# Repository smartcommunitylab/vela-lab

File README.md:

##Smart City Vela Lab
========================

This repository contains the code for the network devices used in the Smart City Lab located in Vela (Trento, Italy).

For cloning:
```bash
git clone https://github.com/smartcommunitylab/vela-lab.git
cd vela-lab
git checkout ota
git submodule init
git submodule update
cd network_board/contiki-ng
git submodule init
git submodule update
```
Some detail about compilation can be found in README-BUILDING.md

The network components are:
- BLE Beacons: Eddystone or CLIMB (https://www.smartcommunitylab.it/climb-en/) proprietary beacons
- Vela Node: composed by:
    - BLE Scanner: Nordic nRF52 DK (nRF52832 SoC) - also referred as Nordic Board
    - Mesh Node: Texas Instruments cc2650/cc1350 launchpad - also referred as TI Board
    - Interface Board (provides mechanical and electrical connection between the BLE Scanner and the Mesh Node, moreover it manages the solar charger and the battery)
- Mesh Sink: Texas Instruments cc2650/cc1350 launchpad or sensortag
- Gateway: Raspberry PI

The purpose of the network is to monitor for the presence of BLE Beacons nearby the Vela Nodes. The list of presence (ble report) is sent to the sink by the means of the multihop network.
For each BLE Beacon detected by a Vela Node an entry is added to the ble report, this entry contains: the eddystone instance ID, the last value of the RSSI, the max value of the RSSI (during the last observation window) and the amount of beacons packets received from that beacon.
The ble report is generated by the BLE Scanner in particular the related code is in (vela-lab/bt_board/ble_app_vela_lab/main.c -> add_node_to_report_payload(...)).

The BLE Scanner and Mesh Node communicate through an interface based on UART periphearl. A specific communication protocol have been developed, the protocol implementation is in vela-lab/common/lib/uart_util.
The same implementation of this protocol (uart_util) is used both in the BLE Scanner and in the Mesh Node, the adaption of the interface with the proprietary stacks (contiki and nRF SDK) is made through macros (#ifdef CONTIKI #else #endif).

The packet format used by uart_util is briefly documented in vela-lab/doc/raw/uart_packet_struct.xlsx. The most important thing here is that the packet (excluding START_CHAR and END_OF_PACKET) is coded as hexadecimal string.
This means that every raw byte to transfer between the nordic and the TI is converted into two ascii characters (two bytes). It is equivalent to the use of sprintf(coded_byte,"%02x",raw_byte). In this way, the packets over the uart will contain only characters '0' (ascii 0x30) to '9' (ascii 0x39) and 'A' (ascii 0x41)  to 'F' (ascii 0x46).
The packet coding with hex string permits to safetly use START_CHAR=STX (ascii 0x02) and END_OF_PACKET='\n' (ascii 0x0A). Before the adoption of this coding, the packet containing a raw value 10 = 0x0A at any position was a problem since 0x0A is '\n' and it was processed as an END_OF_PACKET.
With hex coding a raw 0x0A (1 byte) is converted into two chars, '0' and 'A' which, in ascii are represented by two bytes: {0x30, 0x39}.

By employing the packet structure in uart_packet_struct.xlsx, debug printf output can be safetly merged with uart_util communication on the same UART interface without any (apparent) issues.
Another benefit of this protocol is that the communication can be sniffed and monitored with a standard serial terminal. Typically, when raw bytes are transmitted over a uart, the serial terminals (putty/teraterm) show only garbage, while using hex string any serial monitor can show the frames perfectly.

The types of packet and their payload description are documented in vela-lab/doc/raw/uart_cmd_def_velaLab.xlsx, these are the only commands that are supported in the communication between the TI and the Nordic over the UART interface. 
Even if there are similarities, the UART commands are not the same as the network commands. Network commands are issued by the Mesh Sink to the Mesh Nodes and they are documented in vela-lab/doc/raw/network_commands.xlsx while the actual definition of codes is in /common/inc/network_messages.h

The Mesh Sink is the root of the WSN and it is its the point where data comes out (for instance the bluetooth reports) or goes in (for instance network commands such as setting the keepalive interval).
Regardless the direction (WSN to gateway, or gateway to WSN) for most of the packet types, the sink just passes them, for some (for instance the ota related packets) some procedures, such as the spitting into smaller chunks, are executed.

Finally, the whole system is managed by the Gateway (which can be a standard pc as well as a single board computer such as a Raspberry) connected to the Mesh Sink running a python script (developed for python3).
On the raspberry, the embedded uart (/dev/ttyS0), exposed on the expansion header, can be used directly on the sensortag (given a proper connection of the TX/RX/Power pins).
Alternatively a launchpad can be used since it embeds a uart to usb bridge (typically /dev/ttyACM0), in that case no hardware related operation is required.

Again, the communication protocol over the UART between the Sink and the Gateway exploits hexadecimal string coding. 
The packet structure is as follow (it is not elsewhere documented): `<IPV6_ADDR_16_BYTES*><PAYLOAD_SIZE_1_BYTE><PACKET_TYPE_2_BYTES**><PAYLOAD_N_BYTES***><PAYLOAD_CHECKSUM_1_BYTE><'\n'>`

\* for broadcast packets (most of commands) set it to 0xFFFFFFFFFFFFFFFFFFFF, otherwise the ipv6 address of the destination node (the Sink cannot be addressed)'

\** these are the same as in vela-lab/doc/raw/network_commands.xlsx

\*** the maximum size of this is given by the uart buffer size defined by the SERIAL_LINE_CONF_BUFSIZE, for the Sink this is defined in in vela-lab/network_board/integrate_sender_uart/build_sink.sh.

Since the data is coded with hex string (2 bytes are allocated for each raw byte), the maximum size for the uart packet (including all the fields) is:  SERIAL_LINE_CONF_BUFSIZE/2.

The python script (vela-lab/gateway/dev/sink_integration/main.py) reads the incoming uart data and decode the packets. A basic Command Line interface is implemented, where basic informations about the WSN is displayed on top, while a console shows log messages.
The python script is lauched by navigating to vela-lab/gateway/dev/sink_integration/ and executing "python3 main.py /dev/ttyS0 57600", where /dev/ttyS0 can be changed with the proper port, and 57600 can be changed if the baudrate of the uart is changed on the Sink. However a simpler way is just to launch startup.sh in the repository root. The idea is to permanently store the default launch parameters (serial interface name, baudrate) into that script.
Once the script is launched, as soon as the data start to arrive from the WSN, the terminal interface becomes populated, by pressing h+enter the list of allowed commands is displayed.
Some command have parameters to be set (for instance the BLE scan parameters can be set), however for now the Command Line Interface does not allow to input the parameters that are hardcoded into vela-lab/gateway/dev/sink_integration/main.py (inside USER_INPUT_THREAD)

The collected data is dumped on log files located in vela-lab/gateway/dev/sink_integration/log, these files are then used to process the data.
Data processing analyzes the collected RSSI values between a BLE Beacon and the BLE Scanner, and it aims at detecting and describing proximity events. A proximity event is defined by the sequence of three phases: approaching, stady, moving away.
When such a sequence is detected a proximity event is generated. It is a json object that contains: 
- scannerID: also referred as NodeID. It is the ID of Vela Node that collected the RSSI
- beaconID: the Eddystone instance ID of the detected beacon
- rssi: the maximum RSSI registered during this event
- start_timestamp: when the proximity event started
- end_timestamp: when the proximity event ended
- event_timestamp: when the BLE Beacon was closest to the BLE Scanner (i.e. the timestamp of the maximum rssi)

The algorith that does this detection is written for Octave (Matlab) and it is launched at a given interval (PROCESS_INTERVAL) by vela-lab/gateway/dev/sink_integration/main.py.
Results are written as json object by the Octave process, then the main.py loads that file and pushes the events to the Thingsboard backend interface.

NOTE:
Special mention is required for the OTA feature. Updating the firmware of Mesh Nodes without the debug probe is allowed through OTA process. The procedures are derived from https://marksolters.com/programming/2016/06/07/contiki-ota.html (no more accessible), sources might be here https://github.com/msolters/ota-server.
To prepare a firmware to be downloaded though OTA a set of operation is required, first the firmware is compiled and properly linked, then the firware metadata* are calculated and appended to the firmware itslef.
To do so a special build script has been prepared (vela-lab/network_board/integrate_sender_uart/build_node_ota.sh, the script contains some comments that should be read before executing it), in order to build the same firmware without the OTA build_node_no_ota.sh can be used.

\*metadata are used to verify the firmware and make the OTA 'safe'

To push the firmware on the nodes:
- launch the python script vela-lab/gateway/dev/sink_integration/main.py
- wait all the nodes to get online
- on the python terminal set the keepalive interval to a long value (just type 250+enter, keepalive will be set to 250s, 255 is the maximum)
- edit vela-lab/network_board/integrate_sender_uart/build_node_ota.sh and verify all the parameters, in particular OTA_VERSION (must be higher than what installed) and OTA_PRE_VERIFIED (must be 0 for OTA, 1 when the firmware is flashed with the debug probe).
- compile the firmware by launching `build_node_ota.sh launchpad_vela/cc1350` where the argument is the Contiki BOARD (can be 'launchpad_vela/cc2650' in case of 2.4GHz network).
- if the compilation worked there will be a file called 'vela_node_ota' (with no extension) found in vela-lab/network_board/integrate_sender_uart/
- on the python terminal press f+enter, this will start the OTA procedure. It might be long, really long (10-20 min per node)
- once the OTA procedure is over, all the nodes will be rebooted hopefully with the new firmware. If not retry, sometimes it works perfectly, sometimes the CRC check fails on the node and the new firmware gets discarded. 

**Folder tree**

The folders contained in this repository are used as follow:
- gateway/: contains all the files related to the Gateway. The python script is there, but also the octave algorithm that processes the data to extract proximity events.
- bt_board/: contains the sources for the BLE Scanner (i.e. the Nordic board).
- network_board/: contains all the Contiki projects related to the Mesh Node and Mesh Sink. The main project is integrate_sender_uart, the others are used for testing/debugging. The folder contains also the full Contiki-NG repository (it is a forked one). Also some external modules are here (the bootloader and ota related libraries)
- common/: contains some files used by more than a component. The uart protocol used for the communication between the Mesh Node and the BLE Scanner is here, as well as some other shared definition.
- hardware/: contains the hardware description (connections bentween the Nordic and the TI) together with the Eagle project of the Interface Board
- doc/: contains some raw,unstructured documentation
- backend/: contains code and files strictly related to the backend server which stores data. Namelly it uses Thingsboard as backend interface. In this folder there are some script to querry the database.

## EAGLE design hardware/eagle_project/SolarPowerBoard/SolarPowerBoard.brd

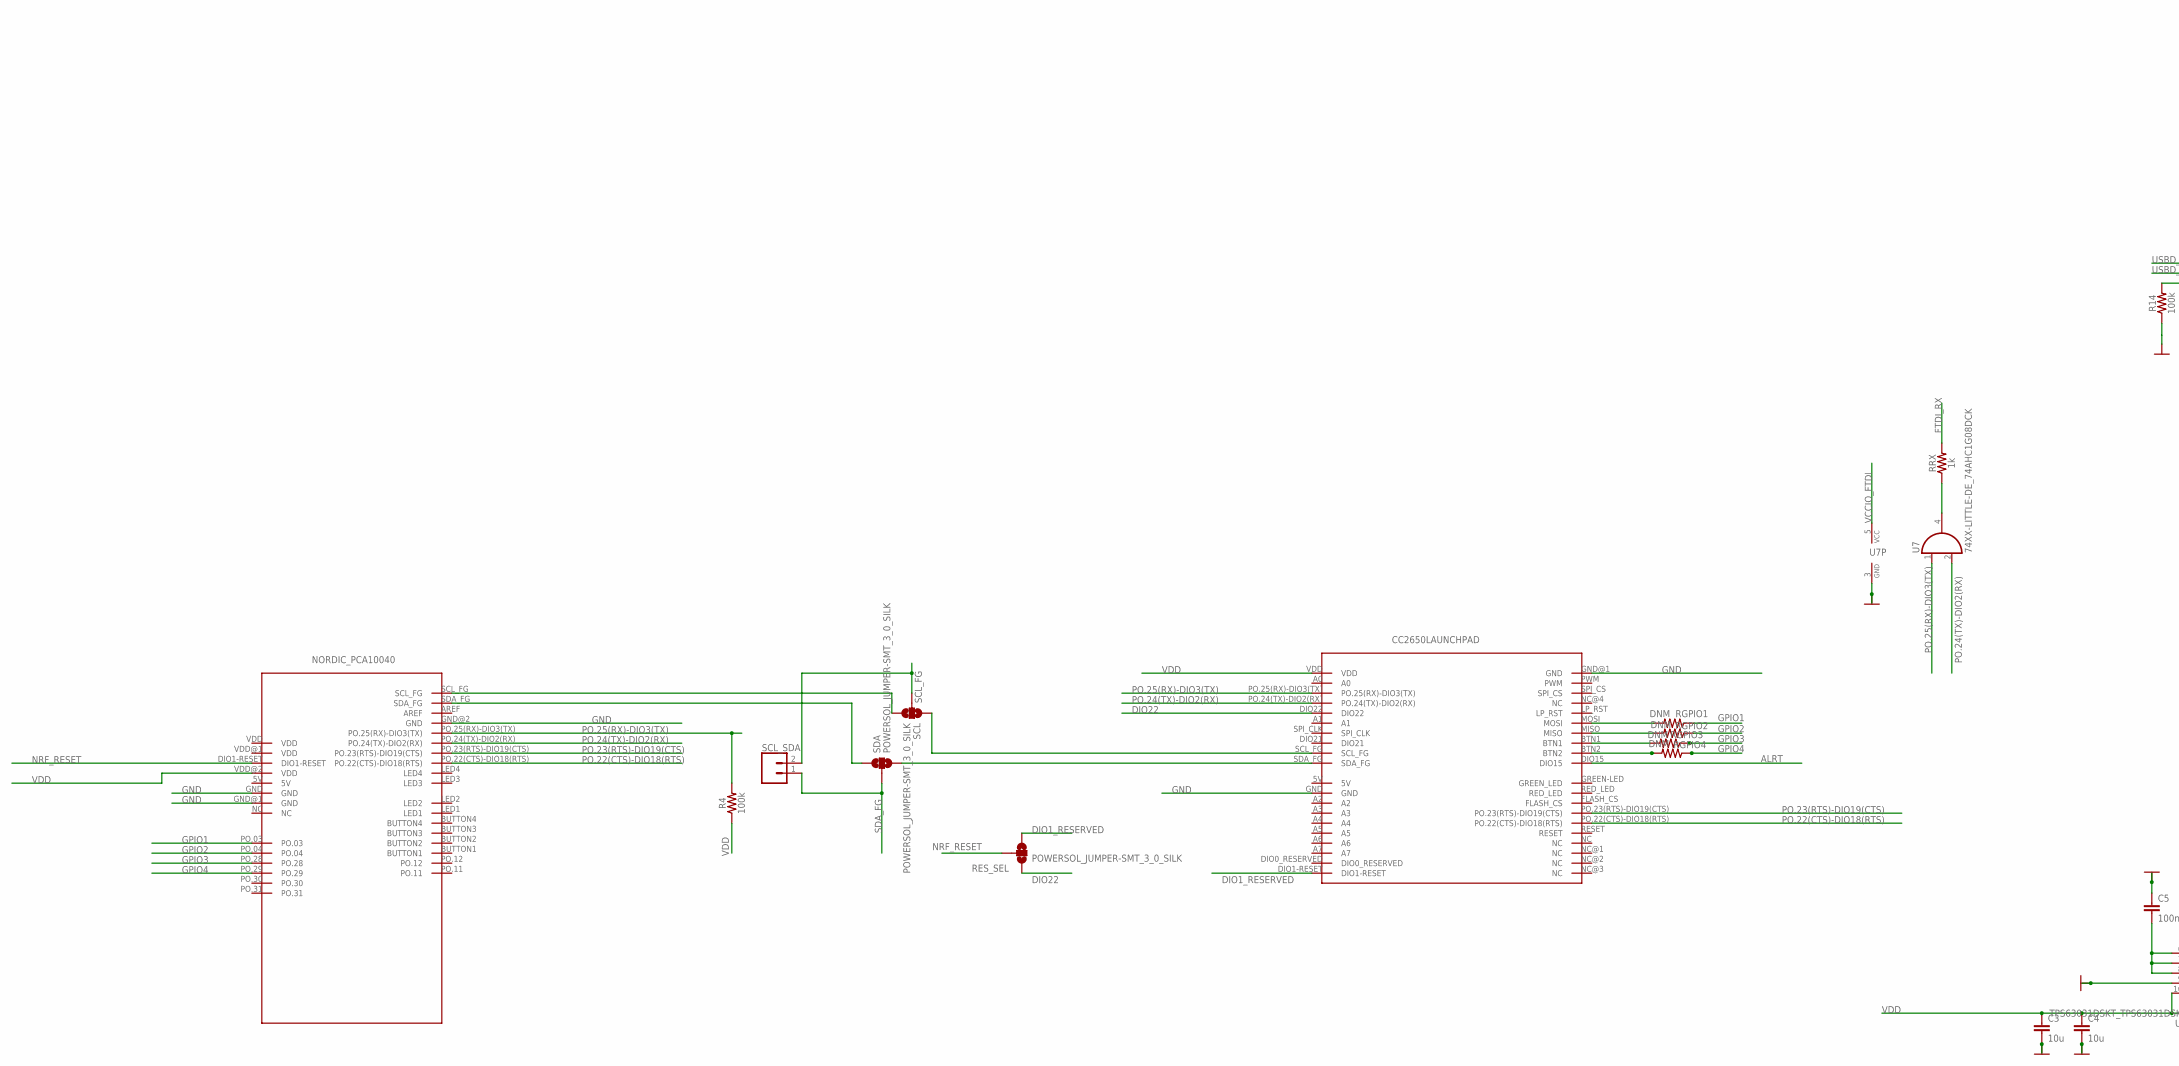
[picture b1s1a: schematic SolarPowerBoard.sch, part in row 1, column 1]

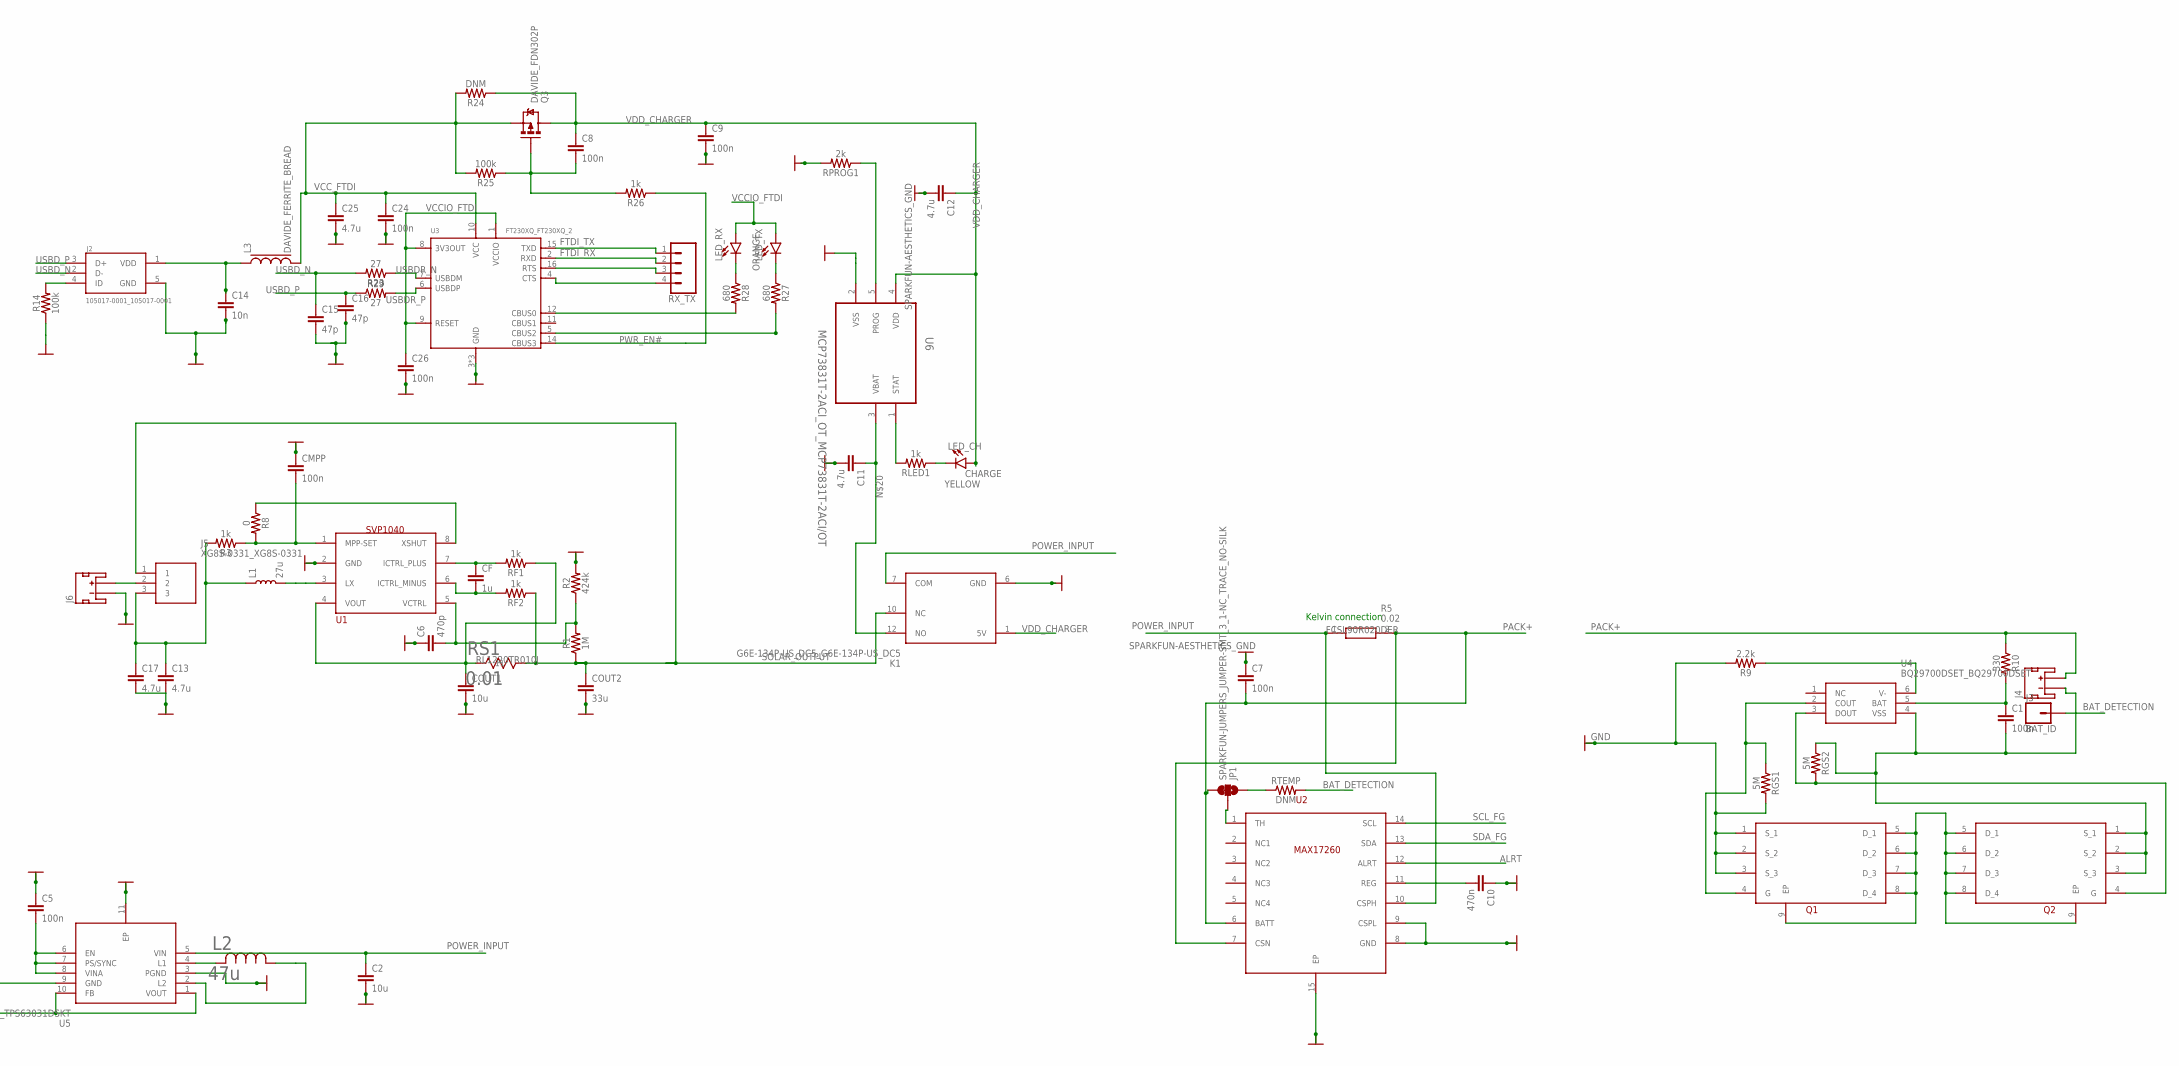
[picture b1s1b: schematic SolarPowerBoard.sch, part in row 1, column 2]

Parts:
B1: POWERSOL_CC2650LAUNCHPAD; POWERSOL_SEPS_RB; MPN LAUNCHXL-CC2650
B2: POWERSOL_PCA10040NORDIC; POWERSOL_SEPS_BB
C1, C5, C7, C8, C9, C24, C26: 100n; SPARKFUN-CAPACITORS_0805; MPN TPSP106M010R2000
C2, C3, C4: 10u; SPARKFUN-CAPACITORS_0805; MPN TPSP106M010R2000
C6: 470p; SPARKFUN-CAPACITORS_0805; MPN TPSP106M010R2000
C10: 470n; SPARKFUN-CAPACITORS_0805; MPN TPSP106M010R2000
C11, C12, C13, C17, C25: 4.7u; SPARKFUN-CAPACITORS_0805; MPN TPSP106M010R2000
C14: 10n; SPARKFUN-CAPACITORS_0805; MPN TPSP106M010R2000
C15, C16: 47p; SPARKFUN-CAPACITORS_0805; MPN TPSP106M010R2000
CF: 1u; SPARKFUN-CAPACITORS_0805; MPN TPSP106M010R2000
CMPP: 100n; SPARKFUN-CAPACITORS_0805; MPN TPSP106M010R2000
COUT1: 10u; SPARKFUN-CAPACITORS_0805; MPN TPSP106M010R2000
COUT2: 33u; SPARKFUN-CAPACITORS_0805; MPN TPSP106M010R2000
J2: 105017-0001_105017-0001; 105017-0001_MOLEX_105017-0001; MPN 105017-0001
J3: BAT_ID; SPARKFUN-CONNECTORS_1X01
J4, J6: SOLARCOMPONENTS_JST_2MM_MALE; SOLARCOMPONENTS_JST-2-SMD
J5: XG8S-0331_XG8S-0331; XG8S-0331_HDRV3W70P0X254_1X3_760X280X680
JP1: SPARKFUN-JUMPERS_JUMPER-SMT_3_1-NC_TRACE_NO-SILK; SPARKFUN-JUMPERS_SMT-JUMPER_3_1-NC_TRACE_NO-SILK
K1: G6E-134P-US_DC5_G6E-134P-US_DC5; G6E-134P-US_DC5_DIP762W60P254L1595H800Q12N
L1: 27u; AXIAL-14MM; MPN B82144F2273K000
L2: 47u; SRN3010-470M_IND_BOURNS_SRN3010; MPN SRN3010-470M
L3: DAVIDE_FERRITE_BREAD; DAVIDE_0805:1; MPN MI0805K601R-10
LED_CH: LED0603; LED-0603
LED_RX: LED0603; LED-0603
LED_TX: LED0603; LED-0603
Q1, Q2: SOLARCOMPONENTS_CSD16406Q3; SOLARCOMPONENTS_CSD16327; MPN CSD16406Q3
Q3: DAVIDE_FDN302P; DAVIDE_SOT23-3
R1: 1M; SPARKFUN-RESISTORS_0805; MPN RLP73N2AR30JTD
R2: 424k; SPARKFUN-RESISTORS_0805; MPN RLP73N2AR30JTD
R3, R26: 1k; SPARKFUN-RESISTORS_0805; MPN RLP73N2AR30JTD
R4, R14, R25: 100k; SPARKFUN-RESISTORS_0805; MPN RLP73N2AR30JTD
R5: 0.02; FCSL90R020DER_FOOTPRINT
R8: 0; SPARKFUN-RESISTORS_0805; MPN RLP73N2AR30JTD
R9: 2.2k; SPARKFUN-RESISTORS_0805; MPN RLP73N2AR30JTD
R10: 330; SPARKFUN-RESISTORS_0805; MPN RLP73N2AR30JTD
R23, R29: 27; SPARKFUN-RESISTORS_0805; MPN RLP73N2AR30JTD
R24: DNM; SPARKFUN-RESISTORS_0805; MPN RLP73N2AR30JTD
R27, R28: 680; SPARKFUN-RESISTORS_0805; MPN RLP73N2AR30JTD
RES_SEL: POWERSOL_JUMPER-SMT_3_0_SILK; POWERSOL_SMT-JUMPER_3_0_NC_TRACE_SILK
RF1, RF2: 1k; SPARKFUN-RESISTORS_0805; MPN RLP73N2AR30JTD
RGPIO1, RGPIO2, RGPIO3, RGPIO4: DNM; SPARKFUN-RESISTORS_0805; MPN RLP73N2AR30JTD
RGS1, RGS2: 5M; SPARKFUN-RESISTORS_0805; MPN RLP73N2AR30JTD
RLED1: 1k; SPARKFUN-RESISTORS_0805; MPN RLP73N2AR30JTD
RPROG1: 2k; SPARKFUN-RESISTORS_0805; MPN RLP73N2AR30JTD
RRX: 1k; SPARKFUN-RESISTORS_0805; MPN RLP73N2AR30JTD
RS1: 0.01; RL1220T-R010-J_RES_1220
RTEMP: DNM; SPARKFUN-RESISTORS_0805; MPN RLP73N2AR30JTD
RX_TX: SPARKFUN-CONNECTORS_CONN_04; SPARKFUN-CONNECTORS_1X04
SCL: POWERSOL_JUMPER-SMT_3_0_SILK; POWERSOL_SMT-JUMPER_3_0_NC_TRACE_SILK
SCL_SDA: SPARKFUN-CONNECTORS_CONN_02; SPARKFUN-CONNECTORS_1X02
SDA: POWERSOL_JUMPER-SMT_3_0_SILK; POWERSOL_SMT-JUMPER_3_0_NC_TRACE_SILK
U1: SOLARCOMPONENTS_SVP1040; SOLARCOMPONENTS_TSSOP-8
U2: SOLARCOMPONENTS_MAX17260; SOLARCOMPONENTS_SON40P300X300X80-15N; MPN MAX17260SEWL+
U3: FT230XQ_FT230XQ_2; FT230XQ_QFN16; MPN FT230XQ-R
U4: BQ29700DSET_BQ29700DSET; BQ29700DSET_SON50P150X150X80-6N; MPN BQ29700DSET
U5: TPS63031DSKT_TPS63031DSKT; TPS63031DSKT_SON50P250X250X80-11N; MPN TPS63031DSKT
U6: MCP73831T-2ACI_OT_MCP73831T-2ACI/OT; MCP73831T-2ACI_OT_SOT95P280X145-5N
U7: 74XX-LITTLE-DE_74AHC1G08DCK; 74XX-LITTLE-DE_SC70-5; MPN SN74AHC1G08DCKR

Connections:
ALRT: B1.DIO15, U2.12 (ALRT)
BAT_DETECTION: J3.1, RTEMP.2
DIO1_RESERVED: B1.DIO1-RESET, RES_SEL.3
DIO22: B1.DIO22, RES_SEL.1
DP5_UART_FTDI_RX: RRX.1, U7.4 (O)
FTDI_RX: RRX.2, RX_TX.2, U3.2 (RXD)
FTDI_TX: RX_TX.1, U3.15 (TXD)
GND: B1.GND, B1.GND@1 (GND), B2.GND, B2.GND@1 (GND), B2.GND@2 (GND), C2.2, C3.2, C4.2, C5.1, C6.1, C7.1, C9.2, C10.1, C11.2, C12.2, C13.2, C14.2, C15.2, C16.2, C17.2, C24.2, C25.2, C26.2, CMPP.1, COUT1.2, COUT2.2, J2.5 (GND), J6.1 (-), J6.P$1 (-), K1.6 (GND), Q1.1 (S_1), Q1.2 (S_2), Q1.3 (S_3), R2.2, R9.2, R14.1, RGS1.2, RPROG1.2, U1.2 (GND), U2.8 (GND), U2.9 (CSPL), U2.15 (EP), U3.3 (GND), U3.13 (GND), U3.17 (GND), U5.3 (PGND), U5.9 (GND), U5.11 (EP), U6.2 (VSS), U7.3 (GND)
GPIO1: B2.PO.03, RGPIO1.1
GPIO2: B2.PO.04, RGPIO2.1
GPIO3: B2.PO.28, RGPIO3.1
GPIO4: B2.PO.29, RGPIO4.1
unnamed: C13.1, C17.1, J5.3, L1.P$1 (1), R3.2
unnamed: RPROG1.1, U6.5 (PROG)
unnamed: CMPP.2, R3.1, R8.2, U1.1 (MPP-SET)
unnamed: R8.1, U1.8 (XSHUT)
unnamed: COUT1.1, RF1.1, RS1.1 (11), U1.4 (VOUT)
unnamed: CF.1, RF1.2, U1.7 (ICTRL_PLUS)
unnamed: CF.2, RF2.2, U1.6 (ICTRL_MINUS)
unnamed: L2.2, U5.4 (L1)
unnamed: LED_CH.C, RLED1.1
unnamed: C6.2, R1.2, R2.1, U1.5 (VCTRL)
unnamed: C5.2, U5.6 (EN), U5.7 (PS/SYNC), U5.8 (VINA)
unnamed: L2.1, U5.2 (L2)
unnamed: RLED1.2, U6.1 (STAT)
unnamed: Q1.5 (D_1), Q1.6 (D_2), Q1.7 (D_3), Q1.8 (D_4), Q1.9 (EP), Q2.5 (D_1), Q2.6 (D_2), Q2.7 (D_3), Q2.8 (D_4), Q2.9 (EP)
unnamed: Q1.4 (G), RGS1.1, U4.2 (COUT)
unnamed: J5.2, J6.2 (+), J6.P$2 (+)
unnamed: JP1.2, U2.1 (TH)
unnamed: L1.P$2 (2), U1.3 (LX)
unnamed: C1.2, J4.1 (-), J4.P$1 (-), Q2.1 (S_1), Q2.2 (S_2), Q2.3 (S_3), RGS2.1, U4.4 (VSS)
unnamed: C11.1, K1.12 (NO), U6.3 (VBAT)
unnamed: JP1.1, RTEMP.1
unnamed: Q2.4 (G), RGS2.2, U4.3 (DOUT)
unnamed: C1.1, R10.2, U4.5 (BAT)
unnamed: C14.1, J2.1 (VDD), L3.1
unnamed: C8.2, Q3.1 (G), R25.1, R26.2
unnamed: J2.4 (ID), R14.2
unnamed: B1.MOSI, RGPIO1.2
unnamed: R9.1, U4.6 (V-)
unnamed: B1.MISO, RGPIO2.2
unnamed: R28.2, U3.12 (CBUS0)
unnamed: LED_RX.C, R28.1
unnamed: B1.BTN1, RGPIO3.2
unnamed: RX_TX.3, U3.16 (RTS)
unnamed: RX_TX.4, U3.4 (CTS)
unnamed: B1.SDA_FG, SDA.3
unnamed: B1.SCL_FG, SCL.1
unnamed: B2.SDA_FG, SDA.1
unnamed: B2.SCL_FG, SCL.3
unnamed: B1.BTN2, RGPIO4.2
unnamed: LED_TX.C, R27.1
unnamed: R27.2, U3.5 (CBUS2)
unnamed: C10.2, U2.11 (REG)
NRF_RESET: B2.DIO1-RESET, RES_SEL.2
PACK+: C7.2, J4.2 (+), J4.P$2 (+), JP1.3, R5.2, R10.1, U2.6 (BATT), U2.7 (CSN)
PO.22(CTS)-DIO18(RTS): B1.PO.22(CTS)-DIO18(RT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, B2.PO.22(CTS)-DIO18(RT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
PO.23(RTS)-DIO19(CTS): B1.PO.23(RTS)-DIO19(CT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, B2.PO.23(RTS)-DIO19(CT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
PO.24(TX)-DIO2(RX): B1.PO.24(TX)-DIO2(RX), B2.PO.24(TX)-DIO2(RX), U7.2 (I1)
PO.25(RX)-DIO3(TX): B1.PO.25(RX)-DIO3(TX), B2.PO.25(RX)-DIO3(TX), R4.2, U7.1 (I0)
POWER_INPUT: C2.1, K1.7 (COM), R5.1, U2.10 (CSPH), U5.5 (VIN)
PWR_EN#: R26.1, U3.14 (CBUS3)
SCL_FG: SCL.2, SCL_SDA.2, U2.14 (SCL)
SDA_FG: SCL_SDA.1, SDA.2, U2.13 (SDA)
SOLAR_OUTPUT: COUT2.1, J5.1, K1.10 (NC), R1.1, RF2.1, RS1.2 (22)
USBDR_N: R23.1, U3.7 (USBDM)
USBDR_P: R29.2, U3.6 (USBDP)
USBD_N: C15.1, J2.2 (D-), R23.2
USBD_P: C16.1, J2.3 (D+), R29.1
VCCIO_FTDI: C26.1, LED_RX.A, LED_TX.A, U3.1 (VCCIO), U3.8 (3V3OUT), U3.9 (RESET), U7.5 (VCC)
VCC_FTDI: C24.1, C25.1, L3.2, Q3.2 (S), R24.2, R25.2, U3.10 (VCC)
VDD: B1.VDD, B2.VDD@2 (VDD), C3.1, C4.1, R4.1, U5.1 (VOUT), U5.10 (FB)
VDD_CHARGER: C8.1, C9.1, C12.1, K1.1 (5V), LED_CH.A, Q3.3 (D), R24.1, U6.4 (VDD)

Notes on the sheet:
Kelvin connection

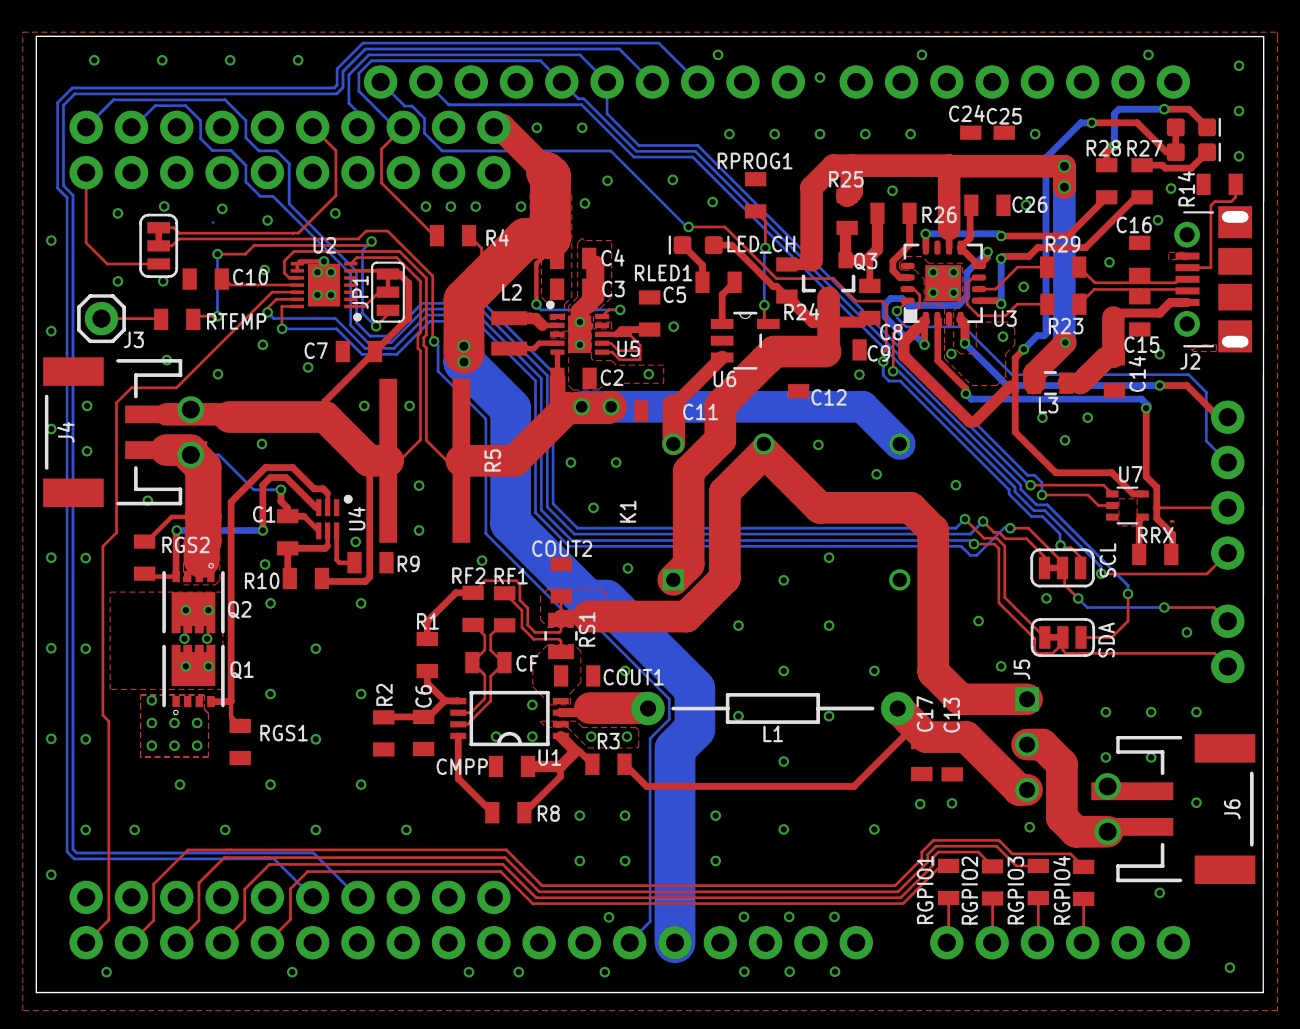
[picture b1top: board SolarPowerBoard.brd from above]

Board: 2 copper layers, 68.8 x 53.6 mm, 83 parts (1 on the bottom side), 73 nets.

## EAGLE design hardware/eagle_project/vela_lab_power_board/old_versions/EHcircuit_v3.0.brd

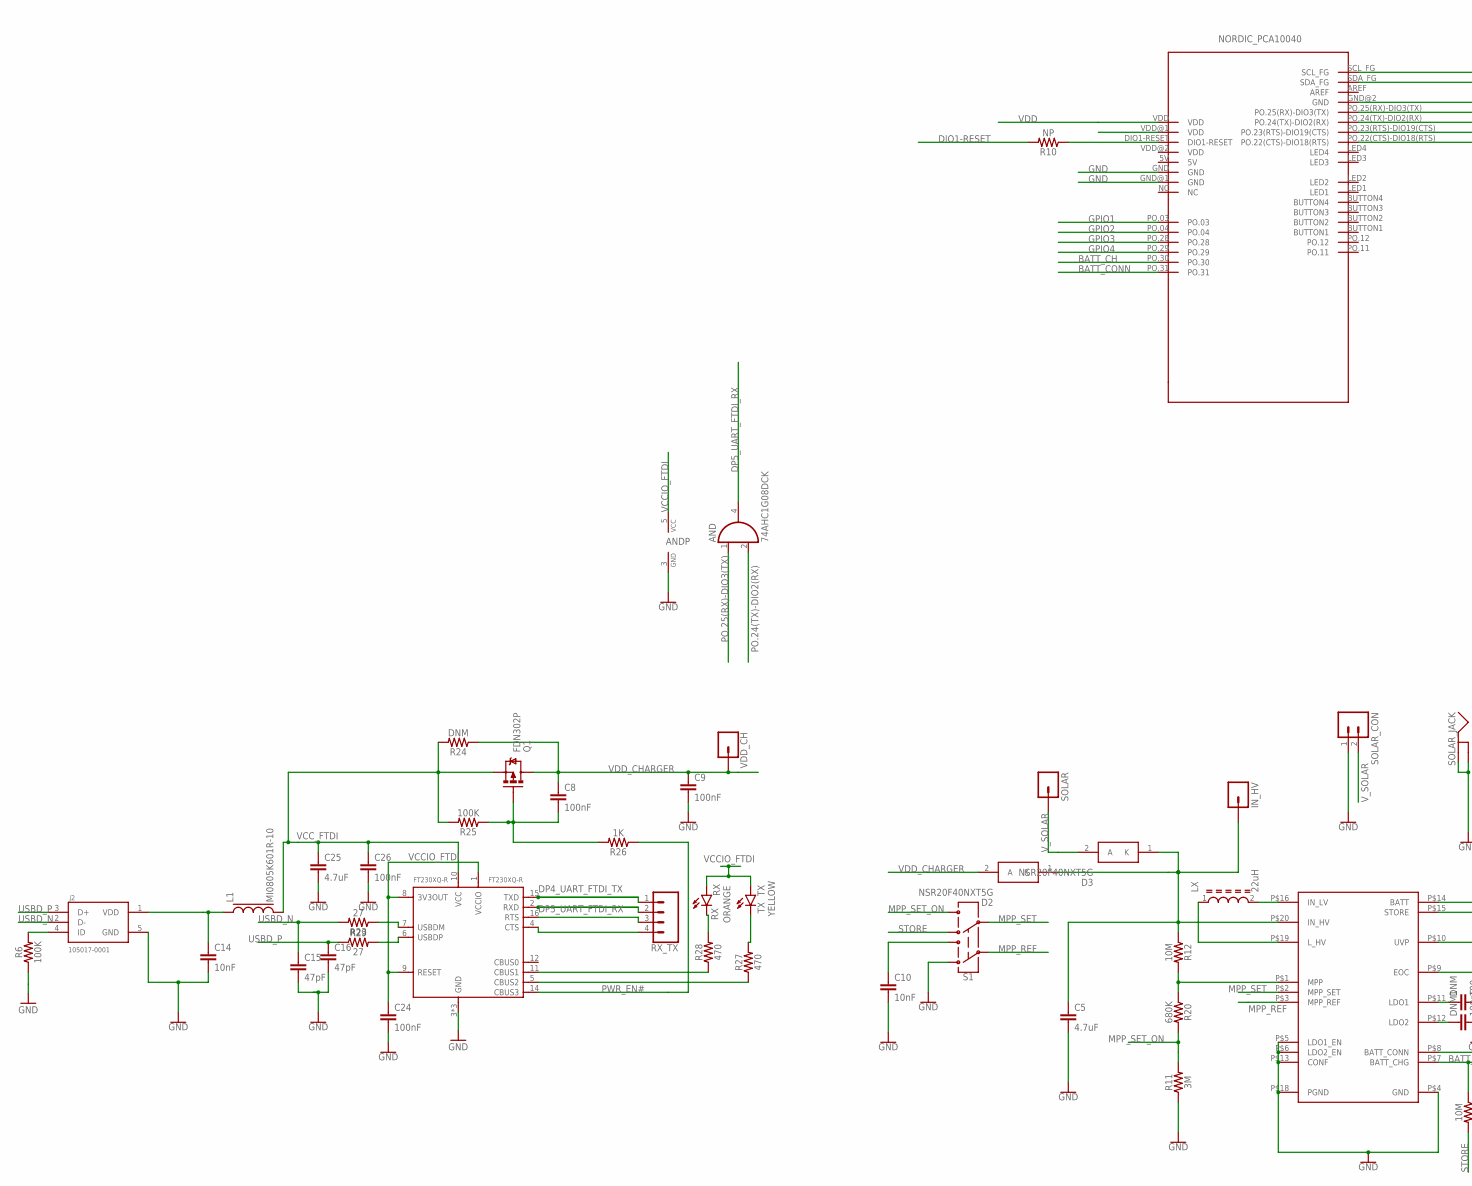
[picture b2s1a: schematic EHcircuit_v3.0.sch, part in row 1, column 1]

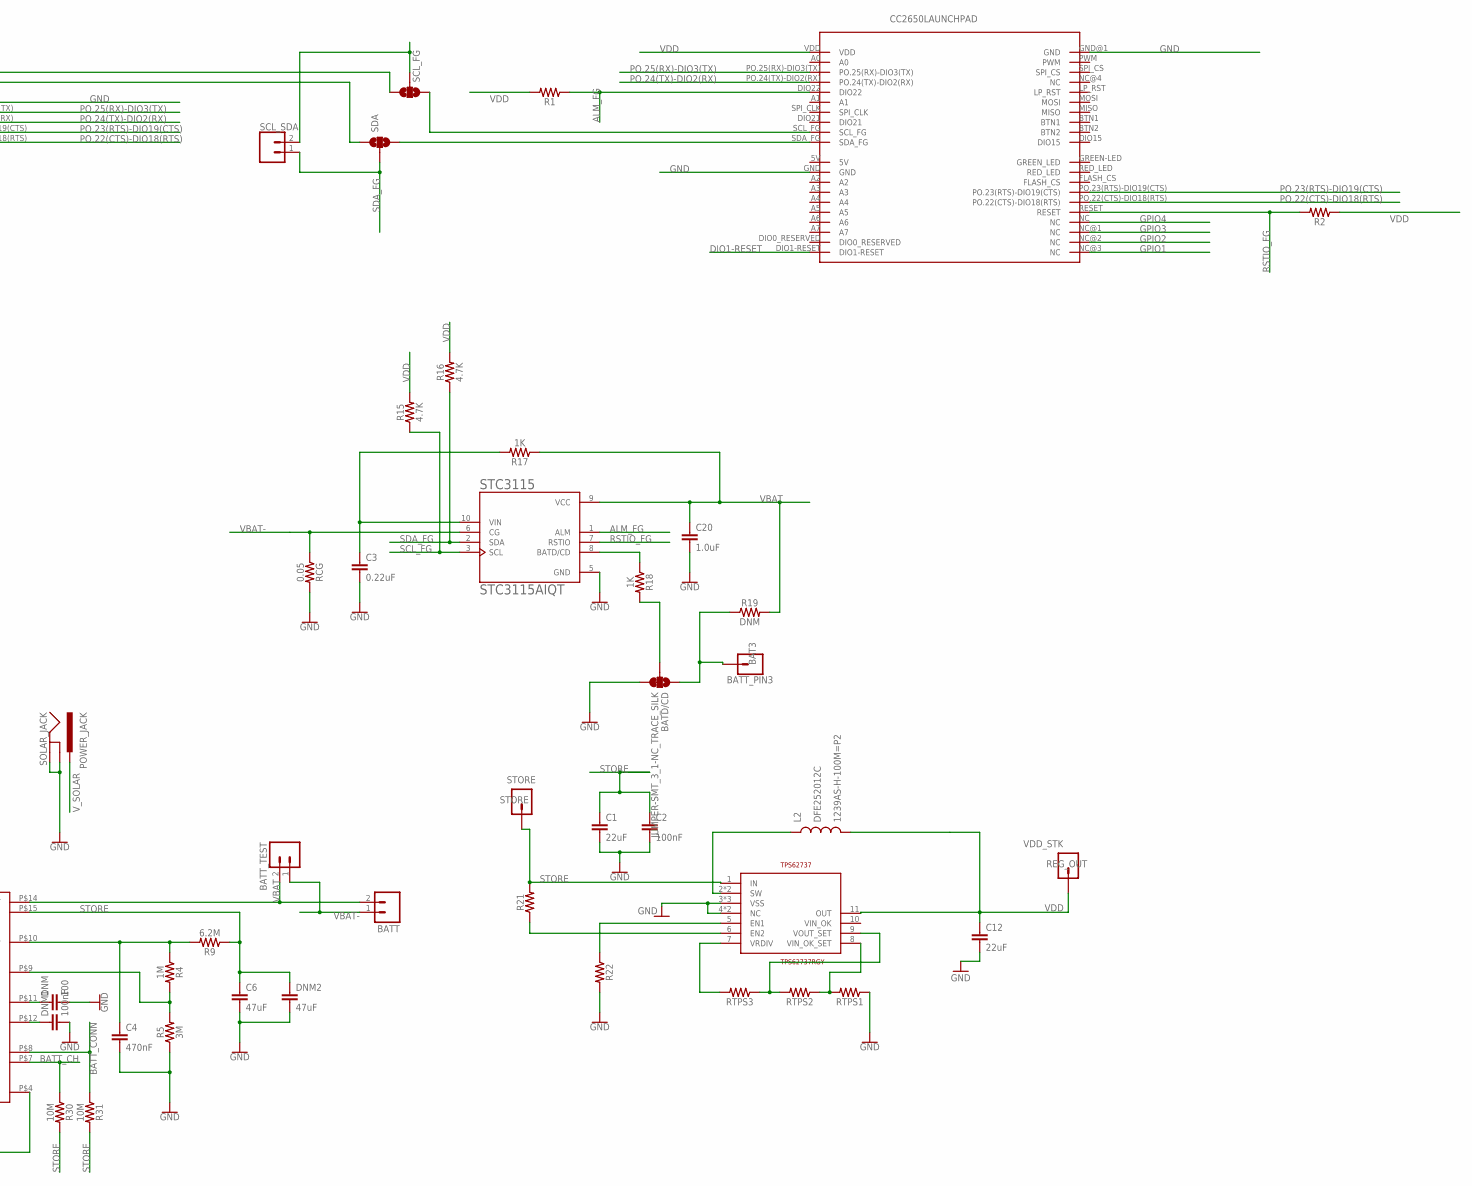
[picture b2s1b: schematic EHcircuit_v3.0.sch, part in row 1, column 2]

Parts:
AND: 74AHC1G08DCK; SC70-5
BAT3: M01PTH; 1X01@1
BATD/CD: JUMPER-SMT_3_1-NC_TRACE_SILK; SMT-JUMPER_3_1-NC_TRACE_SILK
BATT: M02-JST-2MM-SMT; JST-2-SMD@1
BATT_TEST: M02PTH; 1X02@1
C1, C12: 22uF; 0805
C2, C8, C9, C24, C26: 100nF; 0805
C3: 0.22uF; 0805
C4: 470nF; 0805
C5, C25: 4.7uF; 0805
C6: 47uF; 0805
C10, C14: 10nF; 0805
C15, C16: 47pF; 0805
C20: 1.0uF; 0805
D2, D3: NSR20F40NXT5G; DSN2_1
DNM: 100; 0805
DNM1: 100nF; 0805
DNM2: 47uF; 0805
FT230XQ-R: FT230XQ-R; QFN16
IN_HV: M01PTH; 1X01@1
J2: 105017-0001; MOLEX_105017-0001
L1: MI0805K601R-10; 0805
L2: 1239AS-H-100M=P2; DFE252012C
LX: 22uH; INDP4040X180N
Q1: FDN302P; SOT23-3
R1, R2, R21, R22: 0.3OHM-0805-1/8W-1%; 0805
R4: 1M; 0805
R5, R11: 3M; 0805
R6, R25: 100K; 0805
R9: 6.2M; 0805
R10: NP; 0805
R12, R30, R31: 10M; 0805
R15, R16: 4.7K; 0805
R17, R18, R26: 1K; 0805
R19, R24: DNM; 0805
R20: 680K; 0805
R23, R29: 27; 0805
R27, R28: 470; 0805
RB2: CC2650LAUNCHPAD; SEPS_RB
RCG: 0.05; 0805
REG_OUT: M01PTH; 1X01@1
RTPS1, RTPS2, RTPS3: 0.3OHM-0805-1/8W-1%; 0805
RX: ORANGE; LED-0603
RX_TX: CONN_04; 1X04
S1: SWITCH-DPDT-SMD-AYZ0202; SWITCH_DPDT_SMD_AYZ0202
SCL: JUMPER-SMT_3_0_SILK; SMT-JUMPER_3_0_NC_TRACE_SILK
SCL_SDA: CONN_02; 1X02
SDA: JUMPER-SMT_3_0_SILK; SMT-JUMPER_3_0_NC_TRACE_SILK
SOLAR: M01PTH; 1X01@1
SOLAR_CON: M023.5MM; SCREWTERMINAL-3.5MM-2@1
SOLAR_JACK: POWER_JACK; POWER_JACK_PTH
SPV1050: SPV1050
STC3115: STC3115AIQT; SON50P200X300X60-10
STORE: M01PTH; 1X01@1
TPS62737: TPS62737RGY; QFN14
TX: YELLOW; LED-0603
U$1: PCA10040NORDIC; SEPS_BB
VDD_CH: CONN_01; 1X01

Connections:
ALM_FG: R1.1, RB2.DIO22, STC3115.1 (ALM)
BATT_CH: R30.1, SPV1050.P$7 (BATT_CHG), U$1.PO.30
BATT_CONN: R31.1, SPV1050.P$8 (BATT_CONN), U$1.PO.31
DIO1-RESET: R10.2, RB2.DIO1-RESET
DP4_UART_FTDI_TX: FT230XQ-R.15 (TXD), RX_TX.1
DP5_UART_FTDI_RX: AND.4 (O), FT230XQ-R.2 (RXD), RX_TX.2
GND: AND.3 (GND), BATD/CD.3, C1.2, C2.2, C3.2, C4.2, C5.2, C6.2, C9.2, C10.2, C12.2, C14.2, C15.2, C16.2, C20.2, C24.2, C25.2, C26.2, DNM.2, DNM1.2, DNM2.2, FT230XQ-R.3 (GND), FT230XQ-R.13 (GND), FT230XQ-R.17 (GND), J2.5 (GND), R5.1, R6.1, R11.1, R22.2, RB2.GND, RB2.GND@1 (GND), RCG.2, RTPS1.1, S1.1, SOLAR_CON.1, SOLAR_JACK.GND, SOLAR_JACK.GNDBREAK, SPV1050.P$4 (GND), SPV1050.P$5 (LDO1_EN), SPV1050.P$6 (LDO2_EN), SPV1050.P$13 (CONF), SPV1050.P$18 (PGND), STC3115.5 (GND), TPS62737.3 (VSS), TPS62737.4 (NC), TPS62737.12 (VSS), TPS62737.14 (NC), TPS62737.TH_PAD (VSS), U$1.GND, U$1.GND@1 (GND), U$1.GND@2 (GND)
GPIO1: RB2.NC@3 (NC), U$1.PO.03
GPIO2: RB2.NC@2 (NC), U$1.PO.04
GPIO3: RB2.NC@1 (NC), U$1.PO.28
GPIO4: RB2.NC, U$1.PO.29
MPP_REF: S1.2, SPV1050.P$3 (MPP_REF)
MPP_SET: S1.5, SPV1050.P$2 (MPP_SET)
MPP_SET_ON: R11.2, R20.2, S1.6
unnamed: FT230XQ-R.11 (CBUS1), R28.1
unnamed: C14.1, J2.1 (VDD), L1.1
unnamed: C8.2, Q1.1 (G), R25.1, R26.2
unnamed: RTPS1.2, RTPS2.1, TPS62737.8 (VIN_OK_SET)
unnamed: R18.1, STC3115.8 (BATD/CD)
unnamed: R22.1, TPS62737.5 (EN1)
unnamed: LX.2, SPV1050.P$16 (IN_LV)
unnamed: R12.2, R20.1, SPV1050.P$1 (MPP)
unnamed: LX.1, SPV1050.P$19 (L_HV)
unnamed: R21.1, TPS62737.6 (EN2)
unnamed: L2.P$1 (1), TPS62737.2 (SW), TPS62737.13 (SW)
unnamed: RB2.SCL_FG, SCL.1
unnamed: FT230XQ-R.5 (CBUS2), R27.1
unnamed: J2.4 (ID), R6.2
unnamed: R28.2, RX.C
unnamed: R10.1, U$1.DIO1-RESET
unnamed: RTPS3.2, TPS62737.7 (VRDIV)
unnamed: RB2.SDA_FG, SDA.3
unnamed: R27.2, TX.C
unnamed: BATD/CD.2, R18.2
unnamed: RTPS2.2, RTPS3.1, TPS62737.9 (VOUT_SET)
unnamed: SDA.1, U$1.SDA_FG
unnamed: SCL.3, U$1.SCL_FG
unnamed: BAT3.1, BATD/CD.1, R19.1
unnamed: FT230XQ-R.7 (USBDM), R23.1
unnamed: FT230XQ-R.6 (USBDP), R29.2
unnamed: FT230XQ-R.16 (RTS), RX_TX.3
unnamed: C3.1, R17.2, STC3115.10 (VIN)
unnamed: FT230XQ-R.4 (CTS), RX_TX.4
unnamed: C4.1, R4.1, R9.2, SPV1050.P$10 (UVP)
unnamed: R4.2, R5.2, SPV1050.P$9 (EOC)
unnamed: C5.1, D2.1 (K), D3.1 (K), IN_HV.1, R12.1, SPV1050.P$20 (IN_HV)
unnamed: C10.1, S1.3
unnamed: DNM.1, SPV1050.P$11 (LDO1)
unnamed: DNM1.1, SPV1050.P$12 (LDO2)
PO.22(CTS)-DIO18(RTS): RB2.PO.22(CTS)-DIO18(RT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, U$1.PO.22(CTS)-DIO18(RT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
PO.23(RTS)-DIO19(CTS): RB2.PO.23(RTS)-DIO19(CT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, U$1.PO.23(RTS)-DIO19(CT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
PO.24(TX)-DIO2(RX): AND.2 (I1), RB2.PO.24(TX)-DIO2(RX), U$1.PO.24(TX)-DIO2(RX)
PO.25(RX)-DIO3(TX): AND.1 (I0), RB2.PO.25(RX)-DIO3(TX), U$1.PO.25(RX)-DIO3(TX)
PWR_EN#: FT230XQ-R.14 (CBUS3), R26.1
RSTIO_FG: R2.2, RB2.RESET, STC3115.7 (RSTIO)
SCL_FG: R15.1, SCL.2, SCL_SDA.2, STC3115.3 (SCL)
SDA_FG: R16.1, SCL_SDA.1, SDA.2, STC3115.2 (SDA)
STORE: C1.1, C2.1, C6.1, DNM2.1, R9.1, R21.2, R30.2, R31.2, S1.4, SPV1050.P$15 (STORE), STORE.1, TPS62737.1 (IN)
USBD_N: C15.1, J2.2 (D-), R23.2
USBD_P: C16.1, J2.3 (D+), R29.1
VBAT: BATT.2 (1), BATT_TEST.2, C20.1, R17.1, R19.2, SPV1050.P$14 (BATT), STC3115.9 (VCC)
VBAT-: BATT.1 (2), BATT_TEST.1, RCG.1, STC3115.6 (CG)
VCCIO_FTDI: AND.5 (VCC), C24.1, FT230XQ-R.1 (VCCIO), FT230XQ-R.8 (3V3OUT), FT230XQ-R.9 (RESET), RX.A, TX.A
VCC_FTDI: C25.1, C26.1, FT230XQ-R.10 (VCC), L1.2, Q1.2 (S), R24.2, R25.2
VDD: C12.1, L2.P$2 (2), R1.2, R2.1, R15.2, R16.2, RB2.VDD, REG_OUT.1, TPS62737.11 (OUT), U$1.VDD
VDD_CHARGER: C8.1, C9.1, D2.2 (A), Q1.3 (D), R24.1, VDD_CH.1
V_SOLAR: D3.2 (A), SOLAR.1, SOLAR_CON.2, SOLAR_JACK.PWR

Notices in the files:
parts and their libraries:
SparkFun-Connectors: Licensing: Creative Commons ShareAlike 4.0 International - https://creativecommons.org/licenses/by-sa/4.0
